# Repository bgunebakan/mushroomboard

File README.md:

# mushroomboard
Mushroom Board is a single board Computer

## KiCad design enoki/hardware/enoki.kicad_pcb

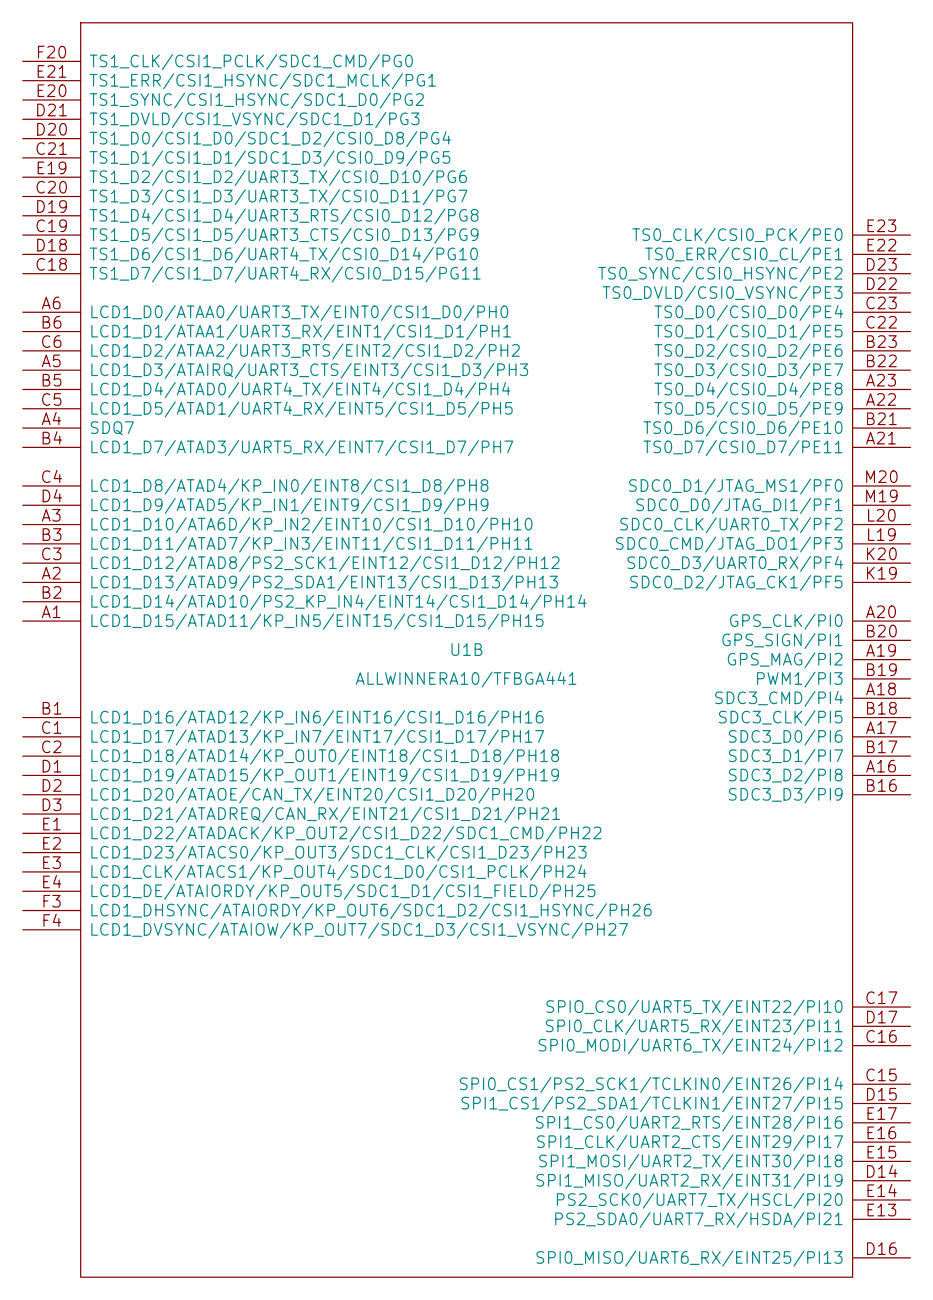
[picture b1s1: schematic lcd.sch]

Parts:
U1: ALLWINNERA10/TFBGA441

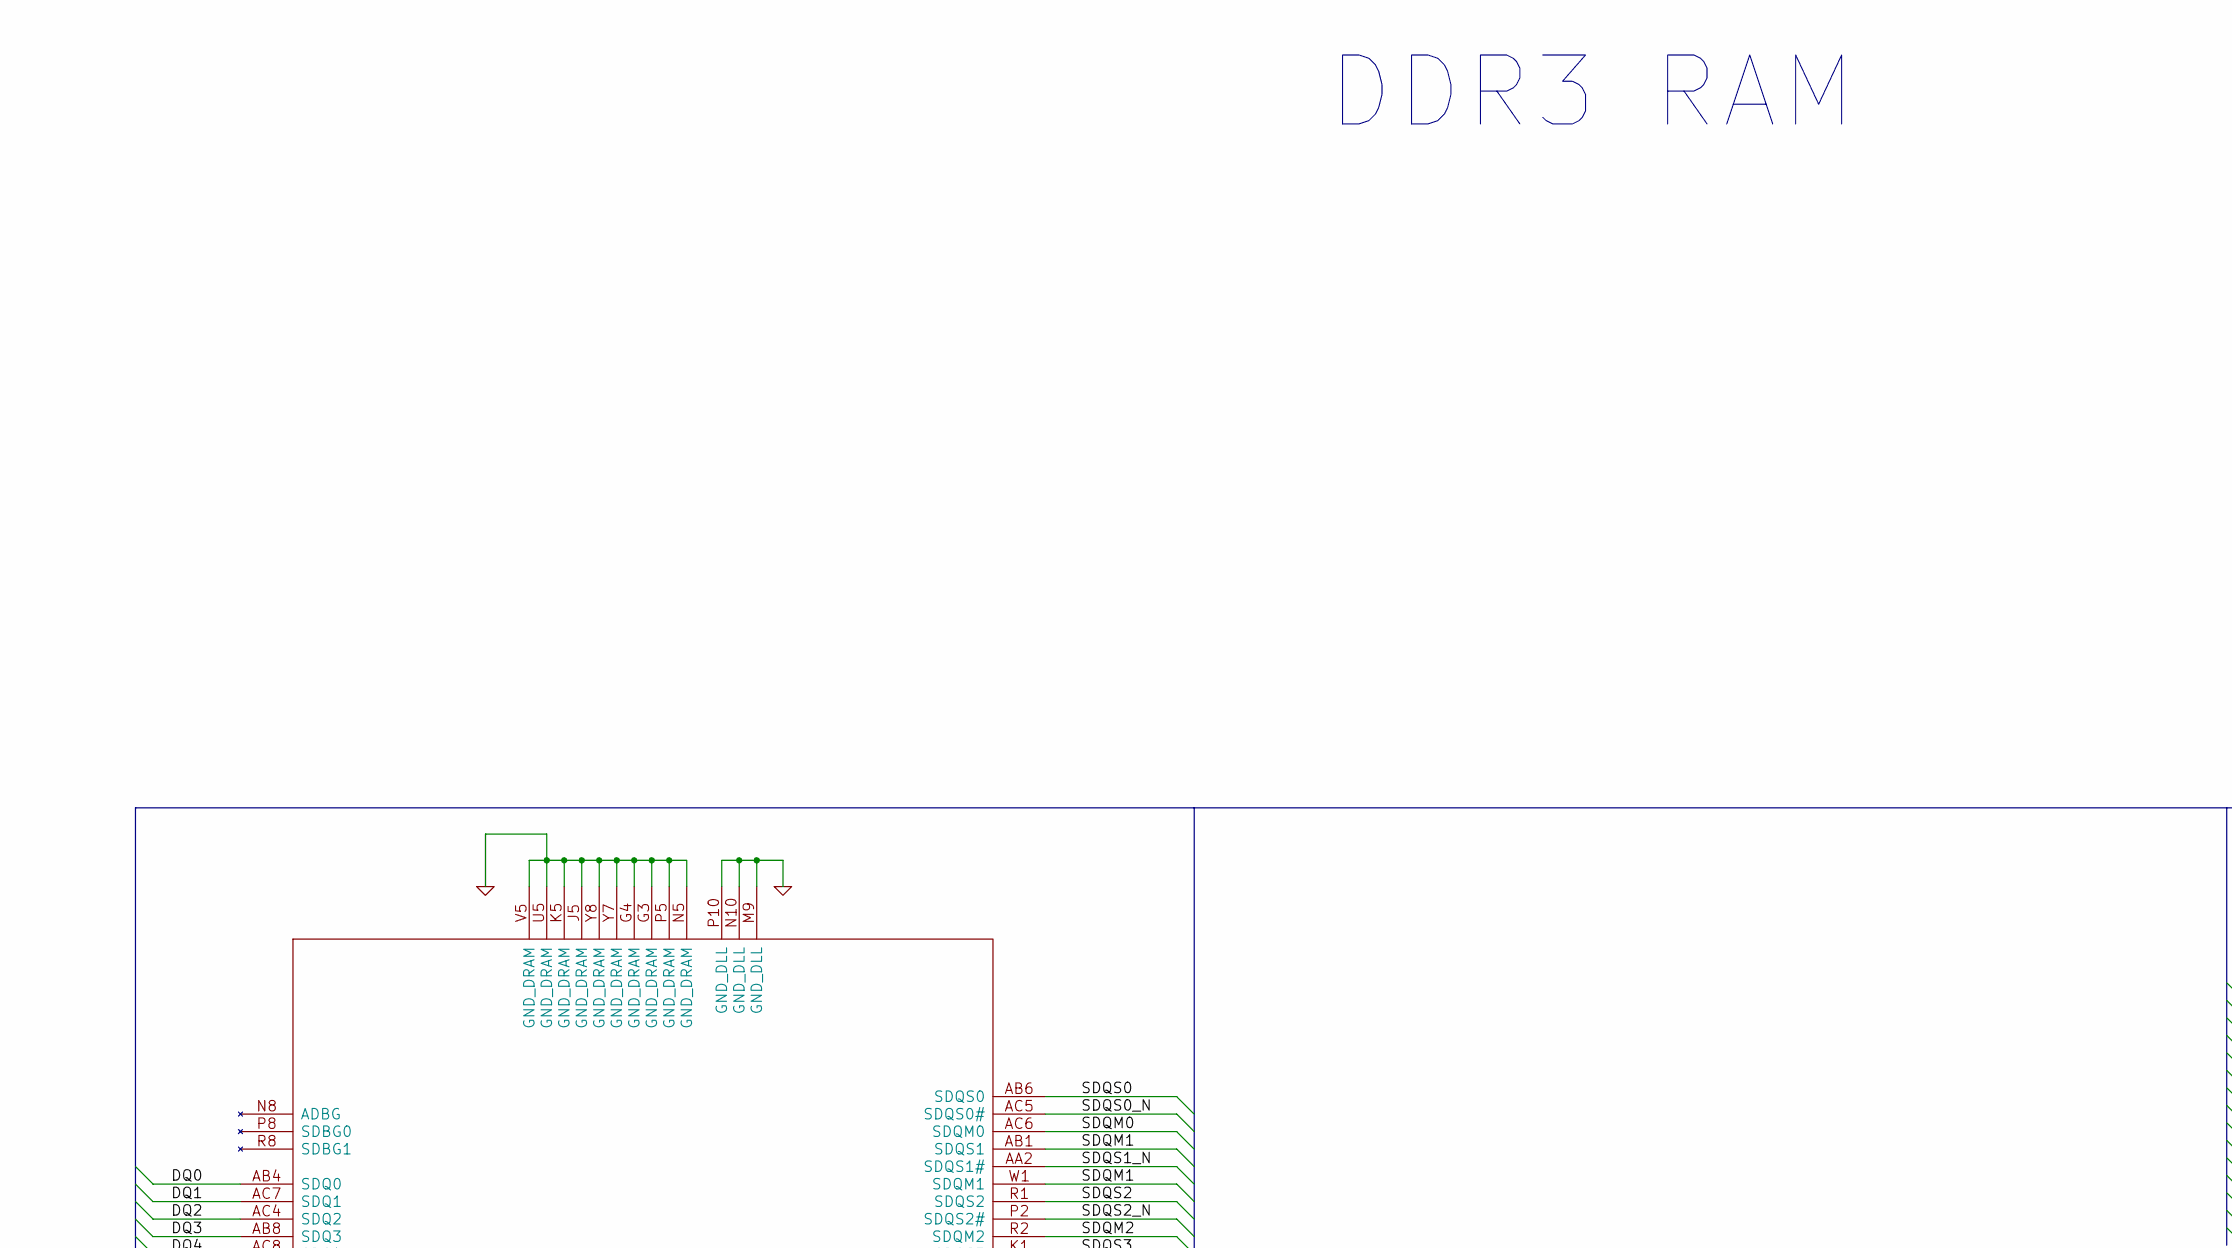
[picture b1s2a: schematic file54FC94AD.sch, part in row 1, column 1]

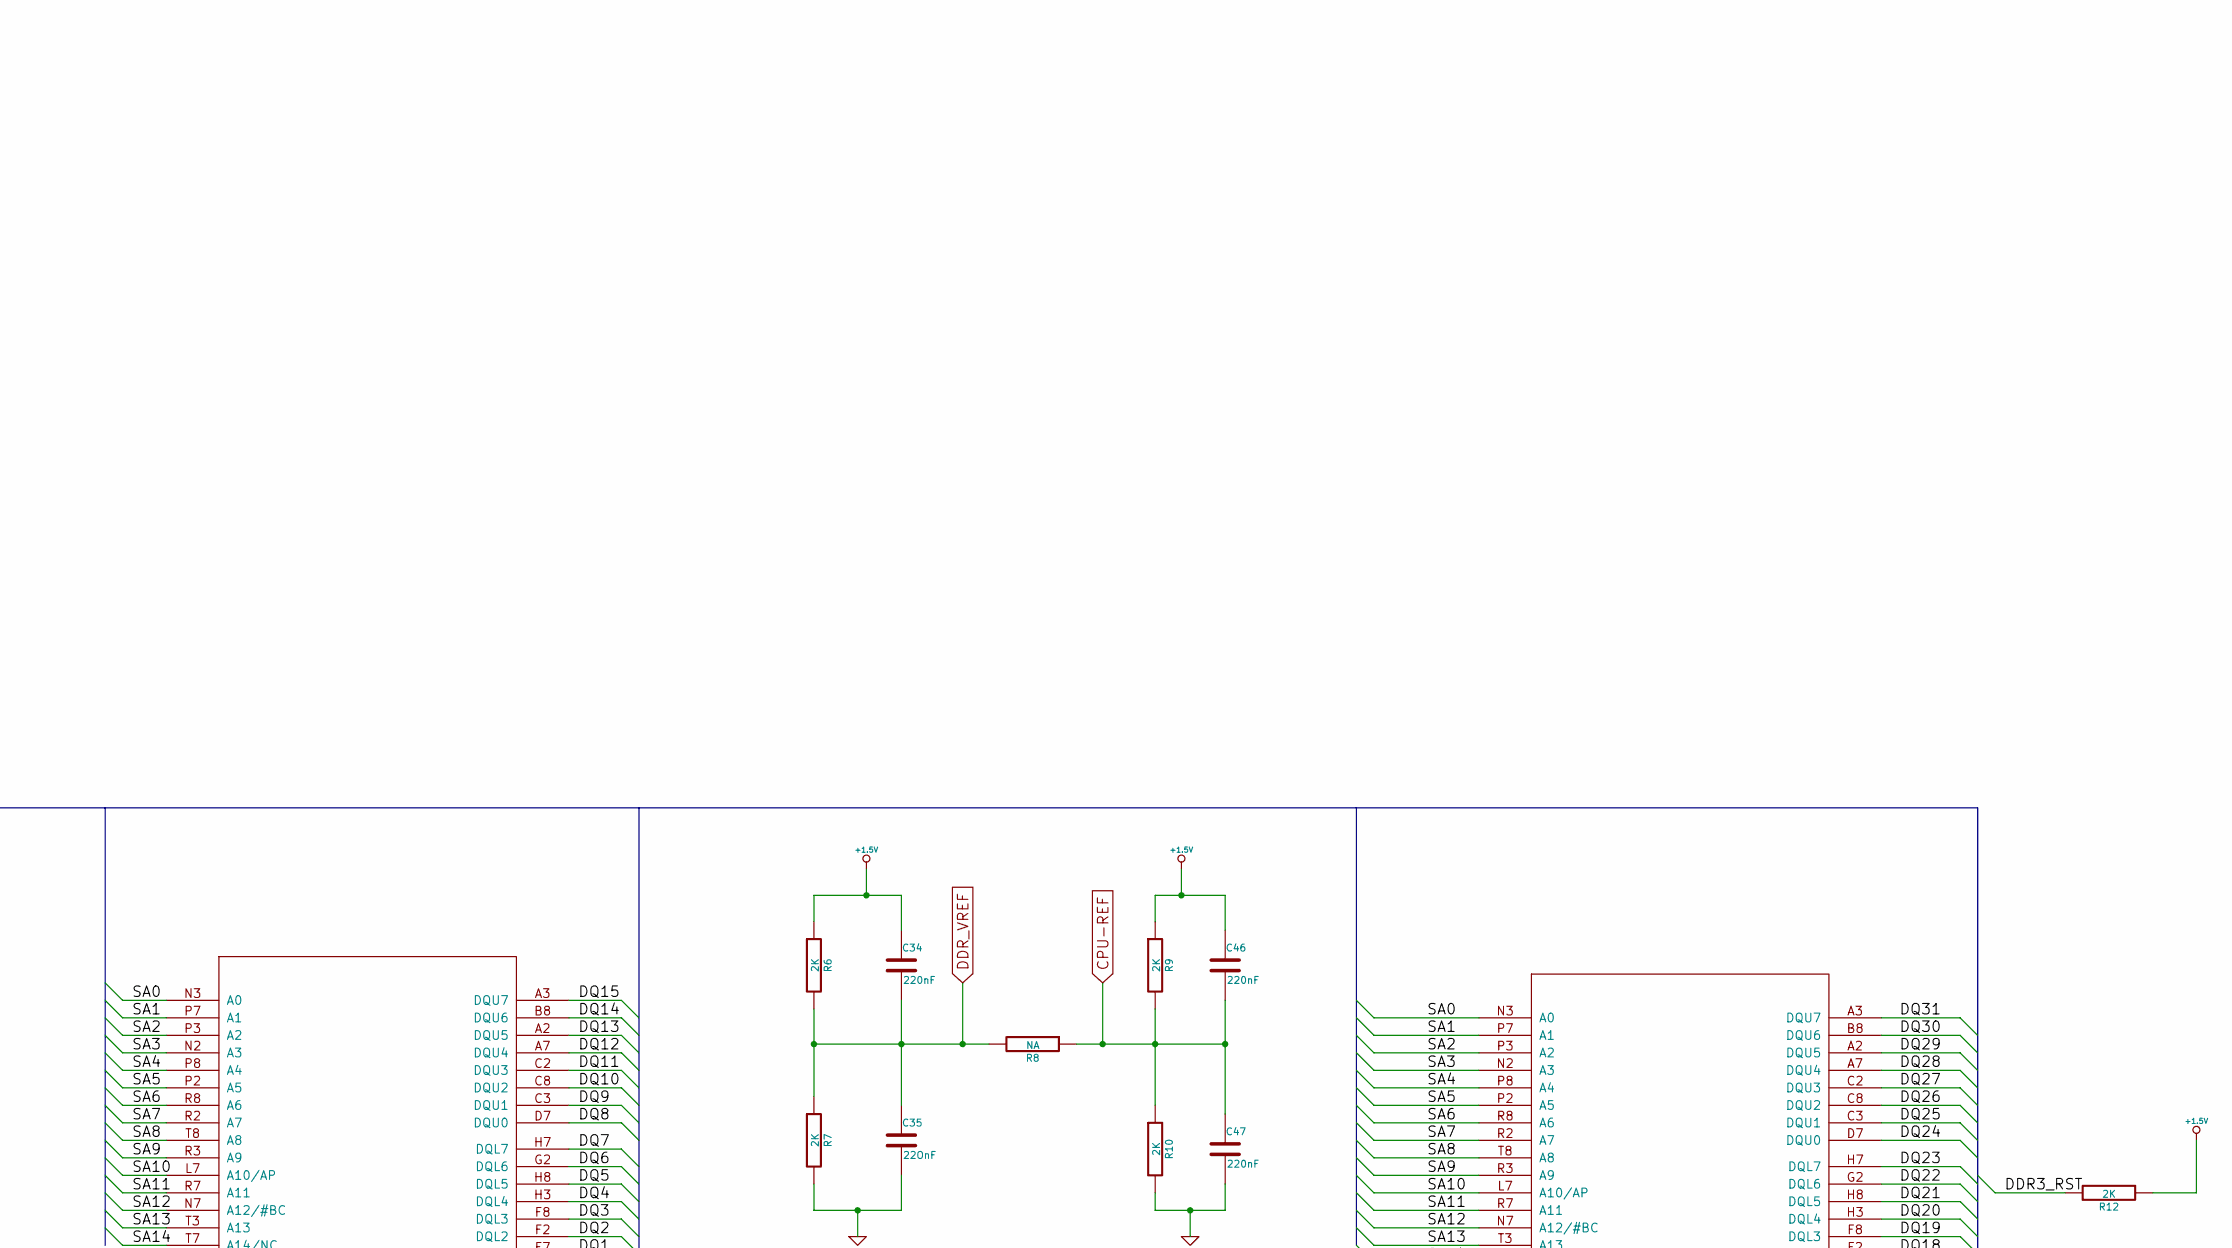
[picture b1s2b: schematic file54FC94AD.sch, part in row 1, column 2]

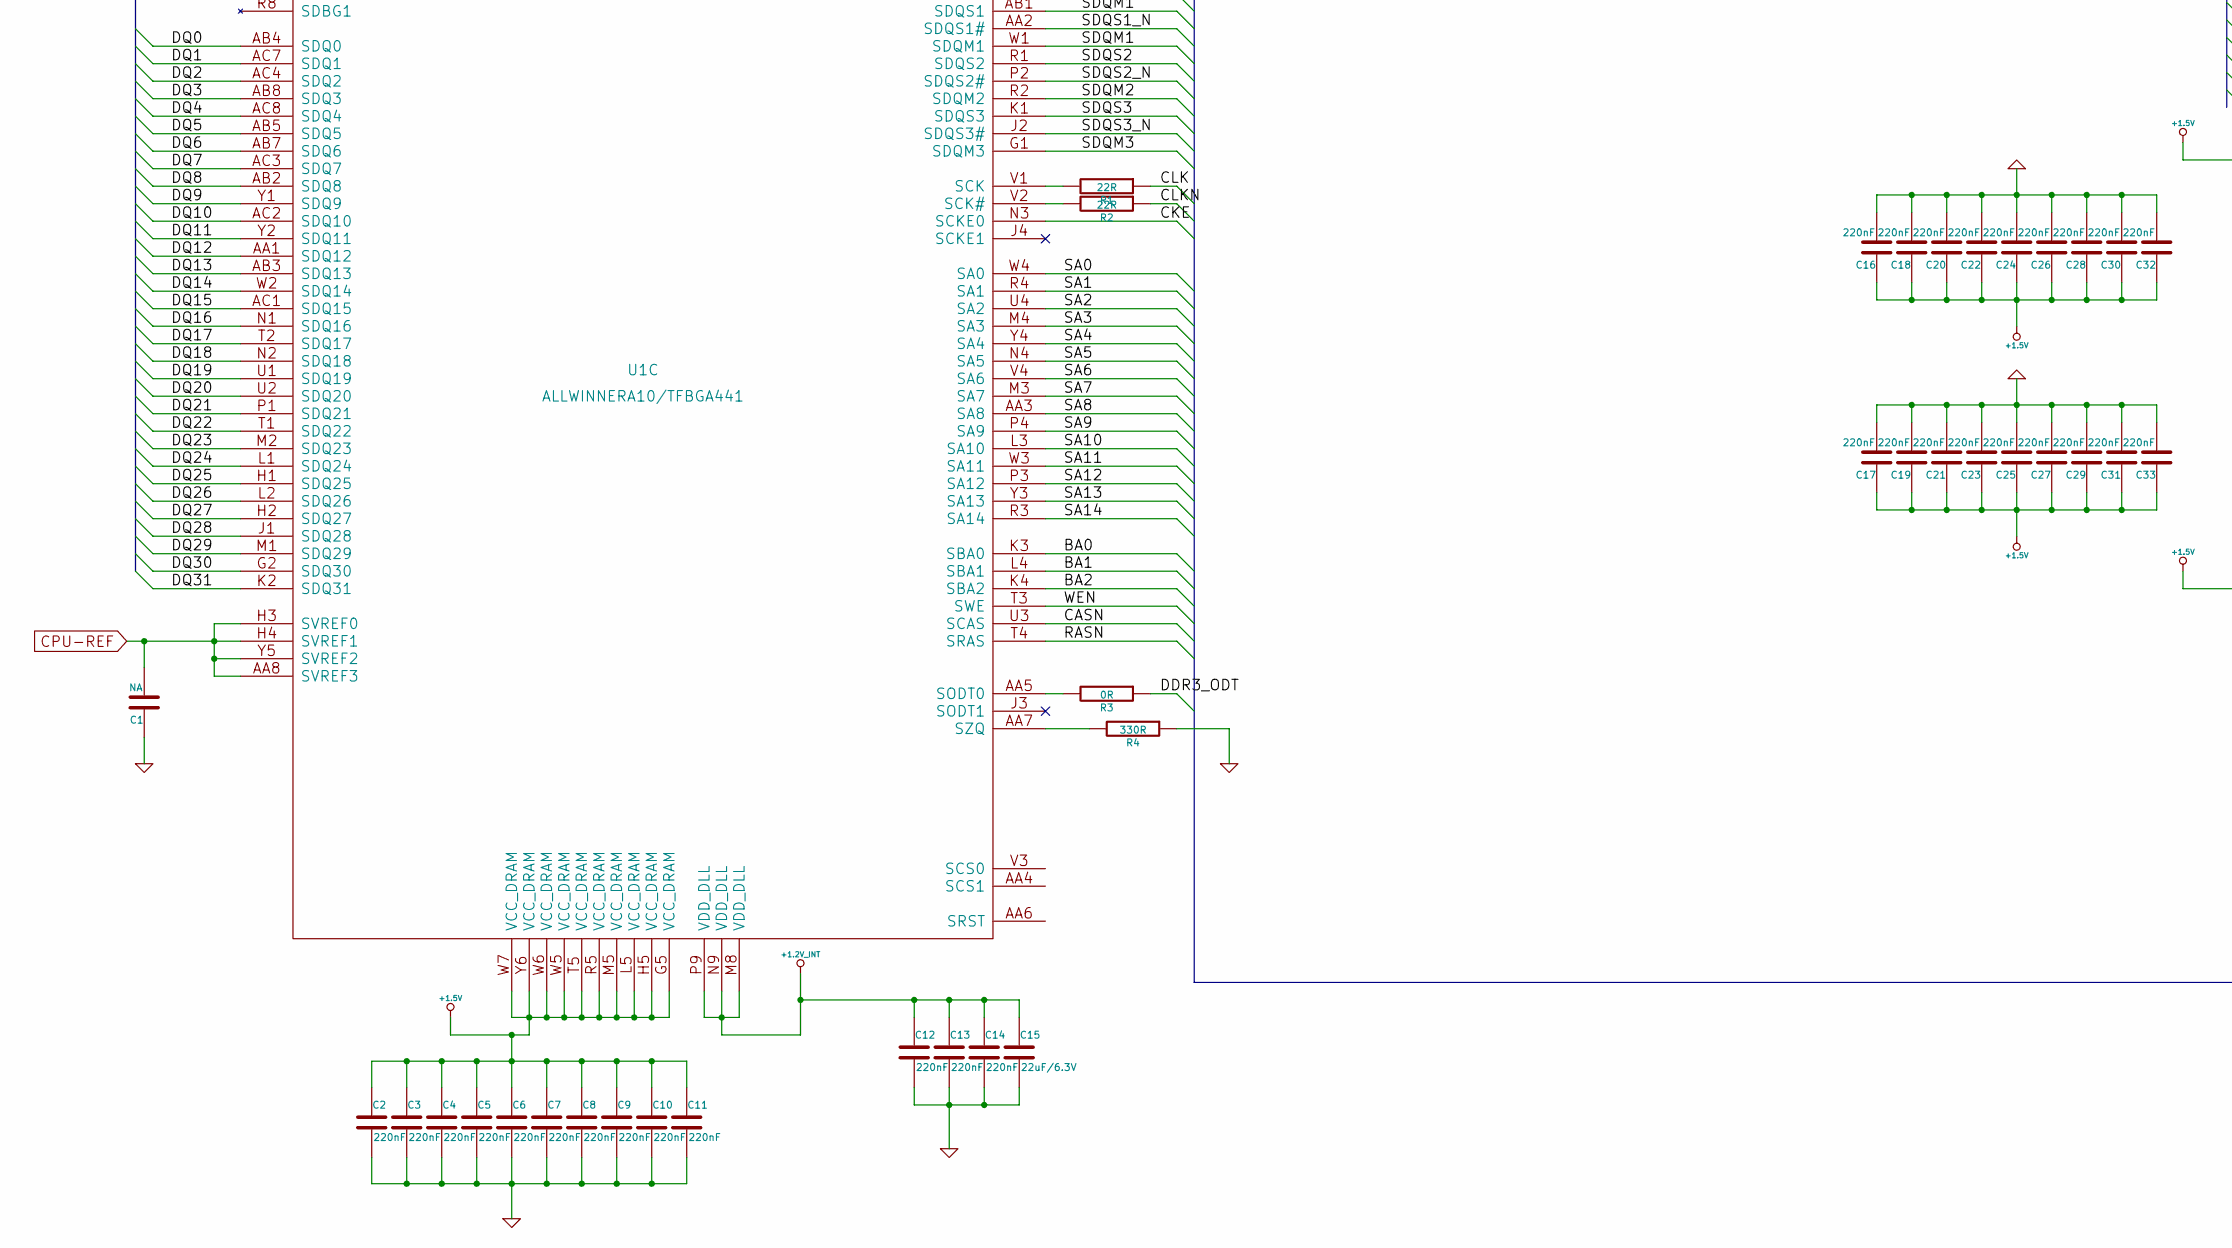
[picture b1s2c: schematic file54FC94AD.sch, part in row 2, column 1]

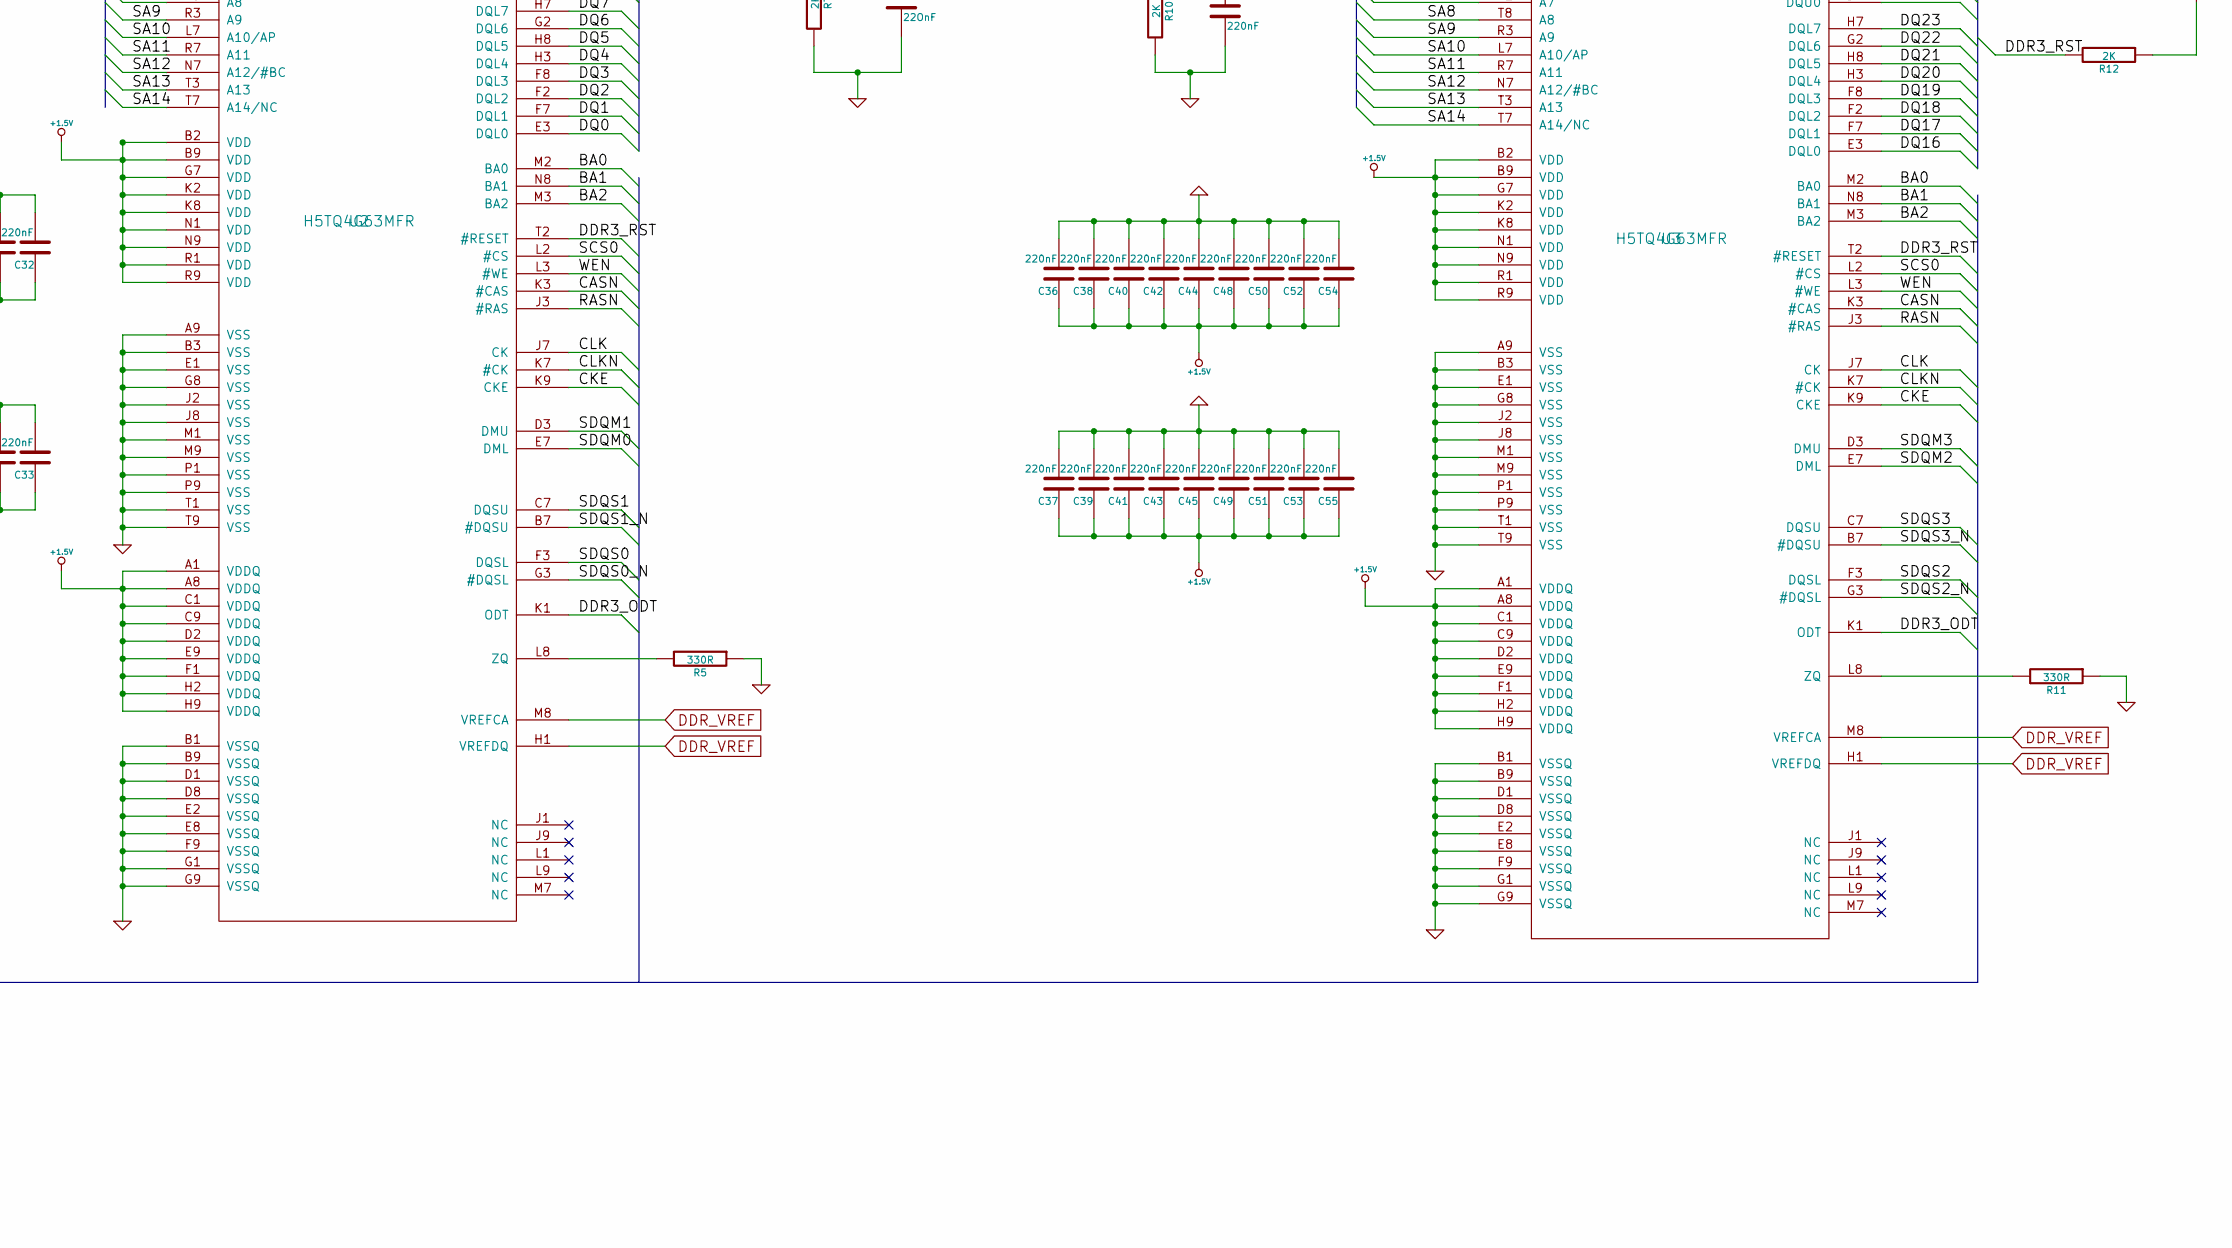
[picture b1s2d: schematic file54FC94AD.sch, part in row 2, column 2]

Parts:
C1: NA
C2, C3, C4, C5, C6, C7, C8, C9, C10, C11, C12, C13, C14, C16, C17, C18, C19, C20, C21, C22, C23, C24, C25, C26, C27, C28, C29, C30, C31, C32, C33, C34, C36, C37, C38, C39, C40, C41, C42, C43, C44, C45, C46, C47, C48, C49, C50, C51, C52, C53, C54, C55: 220nF
C15: 22uF/6.3V
C35: 22OnF
R1, R2: 22R
R3: 0R
R4, R5, R11: 330R
R6, R7, R9, R10, R12: 2K
R8: NA
U1: ALLWINNERA10/TFBGA441
U2, U3: H5TQ4G63MFR

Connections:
+1.2V_INT: C12.1, C13.1, C14.1, C15.1, U1.M8 (VDD_DLL), U1.N9 (VDD_DLL), U1.P9 (VDD_DLL)
/Sheet54FC94AD/BA0: U1.K3 (SBA0), U2.M2 (BA0), U3.M2 (BA0)
/Sheet54FC94AD/BA1: U1.L4 (SBA1), U2.N8 (BA1), U3.N8 (BA1)
/Sheet54FC94AD/BA2: U1.K4 (SBA2), U2.M3 (BA2), U3.M3 (BA2)
/Sheet54FC94AD/CASN: U1.U3 (SCAS), U2.K3 (#CAS), U3.K3 (#CAS)
/Sheet54FC94AD/CKE: U1.N3 (SCKE0), U2.K9 (CKE), U3.K9 (CKE)
/Sheet54FC94AD/CLK: R1.1, U2.J7 (CK), U3.J7 (CK)
/Sheet54FC94AD/CLKN: R2.1, U2.K7 (#CK), U3.K7 (#CK)
/Sheet54FC94AD/DDR3_ODT: R3.1, U2.K1 (ODT), U3.K1 (ODT)
/Sheet54FC94AD/DDR3_RST: R12.2, U2.T2 (#RESET), U3.T2 (#RESET)
/Sheet54FC94AD/DQ0: U1.AB4 (SDQ0), U2.E3 (DQL0)
/Sheet54FC94AD/DQ1: U1.AC7 (SDQ1), U2.F7 (DQL1)
/Sheet54FC94AD/DQ2: U1.AC4 (SDQ2), U2.F2 (DQL2)
/Sheet54FC94AD/DQ3: U1.AB8 (SDQ3), U2.F8 (DQL3)
/Sheet54FC94AD/DQ4: U1.AC8 (SDQ4), U2.H3 (DQL4)
/Sheet54FC94AD/DQ5: U1.AB5 (SDQ5), U2.H8 (DQL5)
/Sheet54FC94AD/DQ6: U1.AB7 (SDQ6), U2.G2 (DQL6)
/Sheet54FC94AD/DQ7: U1.AC3 (SDQ7), U2.H7 (DQL7)
/Sheet54FC94AD/DQ8: U1.AB2 (SDQ8), U2.D7 (DQU0)
/Sheet54FC94AD/DQ9: U1.Y1 (SDQ9), U2.C3 (DQU1)
/Sheet54FC94AD/DQ10: U1.AC2 (SDQ10), U2.C8 (DQU2)
/Sheet54FC94AD/DQ11: U1.Y2 (SDQ11), U2.C2 (DQU3)
/Sheet54FC94AD/DQ12: U1.AA1 (SDQ12), U2.A7 (DQU4)
/Sheet54FC94AD/DQ13: U1.AB3 (SDQ13), U2.A2 (DQU5)
/Sheet54FC94AD/DQ14: U1.W2 (SDQ14), U2.B8 (DQU6)
/Sheet54FC94AD/DQ15: U1.AC1 (SDQ15), U2.A3 (DQU7)
/Sheet54FC94AD/DQ16: U1.N1 (SDQ16), U3.E3 (DQL0)
/Sheet54FC94AD/DQ17: U1.T2 (SDQ17), U3.F7 (DQL1)
/Sheet54FC94AD/DQ18: U1.N2 (SDQ18), U3.F2 (DQL2)
/Sheet54FC94AD/DQ19: U1.U1 (SDQ19), U3.F8 (DQL3)
/Sheet54FC94AD/DQ20: U1.U2 (SDQ20), U3.H3 (DQL4)
/Sheet54FC94AD/DQ21: U1.P1 (SDQ21), U3.H8 (DQL5)
/Sheet54FC94AD/DQ22: U1.T1 (SDQ22), U3.G2 (DQL6)
/Sheet54FC94AD/DQ23: U1.M2 (SDQ23), U3.H7 (DQL7)
/Sheet54FC94AD/DQ24: U1.L1 (SDQ24), U3.D7 (DQU0)
/Sheet54FC94AD/DQ25: U1.H1 (SDQ25), U3.C3 (DQU1)
/Sheet54FC94AD/DQ26: U1.L2 (SDQ26), U3.C8 (DQU2)
/Sheet54FC94AD/DQ27: U1.H2 (SDQ27), U3.C2 (DQU3)
/Sheet54FC94AD/DQ28: U1.J1 (SDQ28), U3.A7 (DQU4)
/Sheet54FC94AD/DQ29: U1.M1 (SDQ29), U3.A2 (DQU5)
/Sheet54FC94AD/DQ30: U1.G2 (SDQ30), U3.B8 (DQU6)
/Sheet54FC94AD/DQ31: U1.K2 (SDQ31), U3.A3 (DQU7)
/Sheet54FC94AD/RASN: U1.T4 (SRAS), U2.J3 (#RAS), U3.J3 (#RAS)
/Sheet54FC94AD/SA0: U1.W4 (SA0), U2.N3 (A0), U3.N3 (A0)
/Sheet54FC94AD/SA1: U1.R4 (SA1), U2.P7 (A1), U3.P7 (A1)
/Sheet54FC94AD/SA2: U1.U4 (SA2), U2.P3 (A2), U3.P3 (A2)
/Sheet54FC94AD/SA3: U1.M4 (SA3), U2.N2 (A3), U3.N2 (A3)
/Sheet54FC94AD/SA4: U1.Y4 (SA4), U2.P8 (A4), U3.P8 (A4)
/Sheet54FC94AD/SA5: U1.N4 (SA5), U2.P2 (A5), U3.P2 (A5)
/Sheet54FC94AD/SA6: U1.V4 (SA6), U2.R8 (A6), U3.R8 (A6)
/Sheet54FC94AD/SA7: U1.M3 (SA7), U2.R2 (A7), U3.R2 (A7)
/Sheet54FC94AD/SA8: U1.AA3 (SA8), U2.T8 (A8), U3.T8 (A8)
/Sheet54FC94AD/SA9: U1.P4 (SA9), U2.R3 (A9), U3.R3 (A9)
/Sheet54FC94AD/SA10: U1.L3 (SA10), U2.L7 (A10/AP), U3.L7 (A10/AP)
/Sheet54FC94AD/SA11: U1.W3 (SA11), U2.R7 (A11), U3.R7 (A11)
/Sheet54FC94AD/SA12: U1.P3 (SA12), U2.N7 (A12/#BC), U3.N7 (A12/#BC)
/Sheet54FC94AD/SA13: U1.Y3 (SA13), U2.T3 (A13), U3.T3 (A13)
/Sheet54FC94AD/SA14: U1.R3 (SA14), U2.T7 (A14/NC), U3.T7 (A14/NC)
/Sheet54FC94AD/SCS0: U2.L2 (#CS), U3.L2 (#CS)
/Sheet54FC94AD/SDQM0: U1.AC6 (SDQM0), U2.E7 (DML)
/Sheet54FC94AD/SDQM1: U1.AB1 (SDQS1), U1.W1 (SDQM1), U2.D3 (DMU)
/Sheet54FC94AD/SDQM2: U1.R2 (SDQM2), U3.E7 (DML)
/Sheet54FC94AD/SDQM3: U1.G1 (SDQM3), U3.D3 (DMU)
/Sheet54FC94AD/SDQS0: U1.AB6 (SDQS0), U2.F3 (DQSL)
/Sheet54FC94AD/SDQS0_N: U1.AC5 (SDQS0#), U2.G3 (#DQSL)
/Sheet54FC94AD/SDQS1: U2.C7 (DQSU)
/Sheet54FC94AD/SDQS1_N: U1.AA2 (SDQS1#), U2.B7 (#DQSU)
/Sheet54FC94AD/SDQS2: U1.R1 (SDQS2), U3.F3 (DQSL)
/Sheet54FC94AD/SDQS2_N: U1.P2 (SDQS2#), U3.G3 (#DQSL)
/Sheet54FC94AD/SDQS3: U1.K1 (SDQS3), U3.C7 (DQSU)
/Sheet54FC94AD/SDQS3_N: U1.J2 (SDQS3#), U3.B7 (#DQSU)
/Sheet54FC94AD/WEN: U1.T3 (SWE), U2.L3 (#WE), U3.L3 (#WE)
CPU-REF: C1.2, C46.2, C47.1, R8.1, R9.2, R10.1, U1.AA8 (SVREF3), U1.H3 (SVREF0), U1.H4 (SVREF1), U1.Y5 (SVREF2)
DDR_VREF: C34.2, C35.1, R6.2, R7.1, R8.2, U2.H1 (VREFDQ), U2.M8 (VREFCA), U3.H1 (VREFDQ), U3.M8 (VREFCA)
unnamed: R1.2, U1.V1 (SCK)
unnamed: R2.2, U1.V2 (SCK#)
unnamed: R3.2, U1.AA5 (SODT0)
unnamed: R4.2, U1.AA7 (SZQ)
unnamed: R5.2, U2.L8 (ZQ)
unnamed: R11.2, U3.L8 (ZQ)

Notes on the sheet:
DDR3 RAM

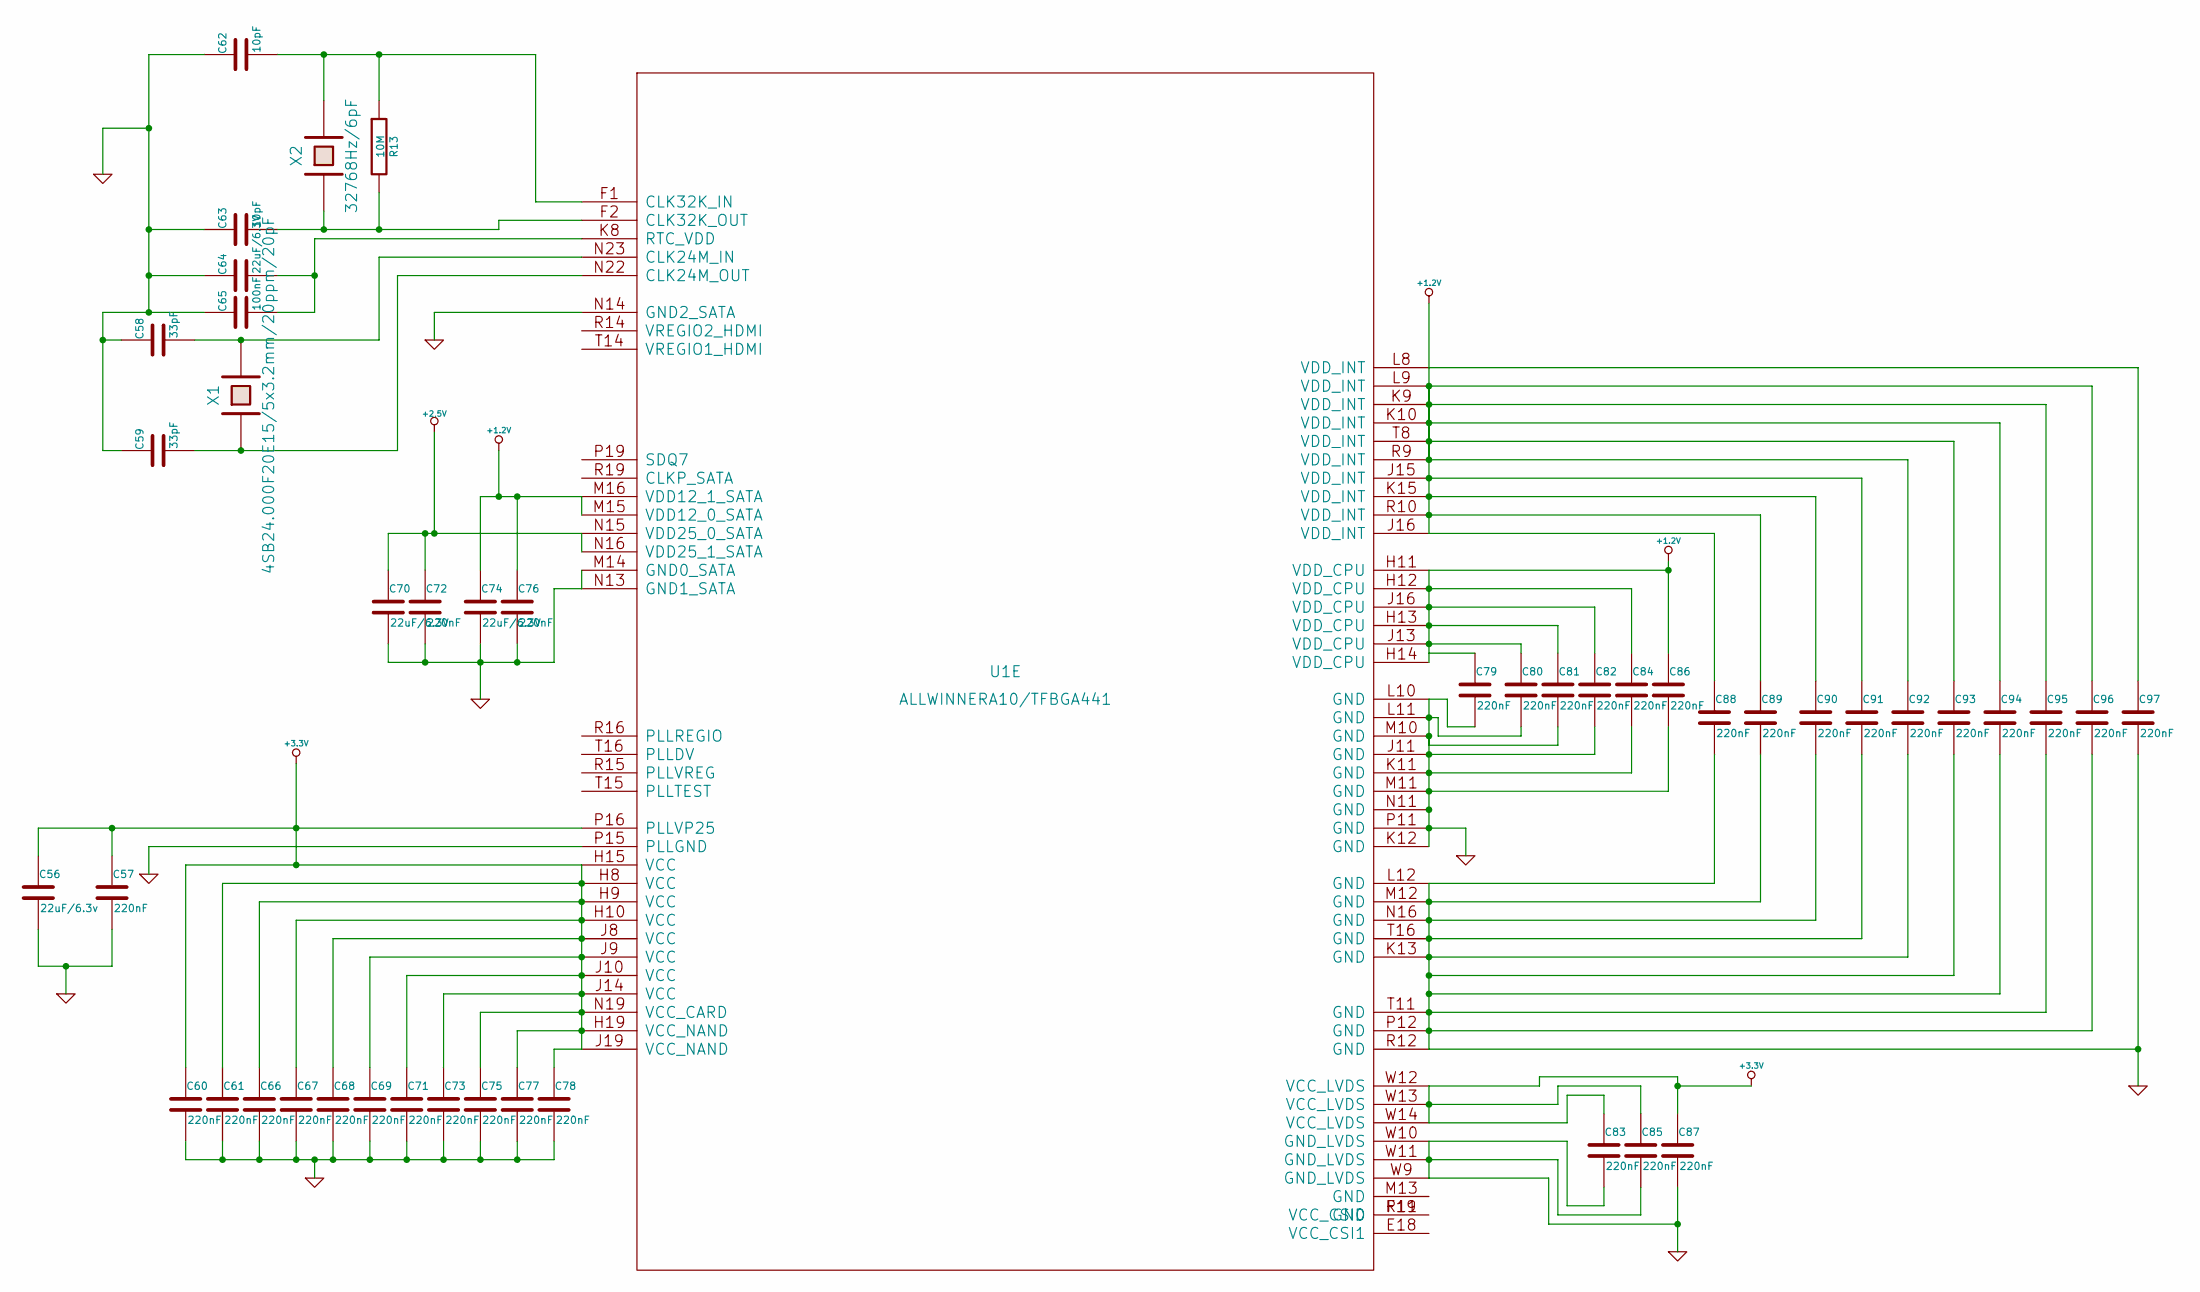
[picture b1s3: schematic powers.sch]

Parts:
C56: 22uF/6.3v
C57, C60, C61, C66, C67, C68, C69, C71, C72, C73, C75, C76, C77, C78, C79, C80, C81, C82, C83, C84, C85, C86, C87, C88, C89, C90, C91, C92, C93, C94, C95, C96, C97: 220nF
C58, C59: 33pF
C62, C63: 10pF
C64, C70, C74: 22uF/6.3V
C65: 100nF
R13: 10M
U1: ALLWINNERA10/TFBGA441
X1: 4SB24.000F20E15/5x3.2mm/20ppm/20pF
X2: 32768Hz/6pF

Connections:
+1.2V: C74.1, C76.1, C80.1, C81.1, C82.1, C84.1, C86.1, C88.1, C89.1, C90.1, C91.1, C92.1, C93.1, C94.1, C95.1, C96.1, U1.H11 (VDD_CPU), U1.H12 (VDD_CPU), U1.H13 (VDD_CPU), U1.H14 (VDD_CPU), U1.J13 (VDD_CPU), U1.J15 (VDD_INT), U1.J16 (VDD_CPU), U1.K9 (VDD_INT), U1.K10 (VDD_INT), U1.K15 (VDD_INT), U1.L9 (VDD_INT), U1.M15 (VDD12_0_SATA), U1.M16 (VDD12_1_SATA), U1.R9 (VDD_INT), U1.R10 (VDD_INT), U1.T8 (VDD_INT)
+3.3V: C56.1, C57.1, C60.1, C61.1, C66.1, C67.1, C68.1, C69.1, C71.1, C73.1, C75.1, C77.1, C78.1, C83.1, C85.1, C87.1, U1.H8 (VCC), U1.H9 (VCC), U1.H10 (VCC), U1.H15 (VCC), U1.H19 (VCC_NAND), U1.J8 (VCC), U1.J9 (VCC), U1.J10 (VCC), U1.J14 (VCC), U1.J19 (VCC_NAND), U1.N19 (VCC_CARD), U1.P16 (PLLVP25), U1.W12 (VCC_LVDS), U1.W13 (VCC_LVDS), U1.W14 (VCC_LVDS)
unnamed: C58.2, U1.N23 (CLK24M_IN), X1.2
unnamed: C59.2, U1.N22 (CLK24M_OUT), X1.1
unnamed: C62.2, R13.1, U1.F1 (CLK32K_IN), X2.2
unnamed: C63.2, R13.2, U1.F2 (CLK32K_OUT), X2.1
unnamed: C64.2, C65.2, U1.K8 (RTC_VDD)
unnamed: C97.1, U1.L8 (VDD_INT)
unnamed: U1.F19 (VCC_CSI0), U1.R11 (GND)

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
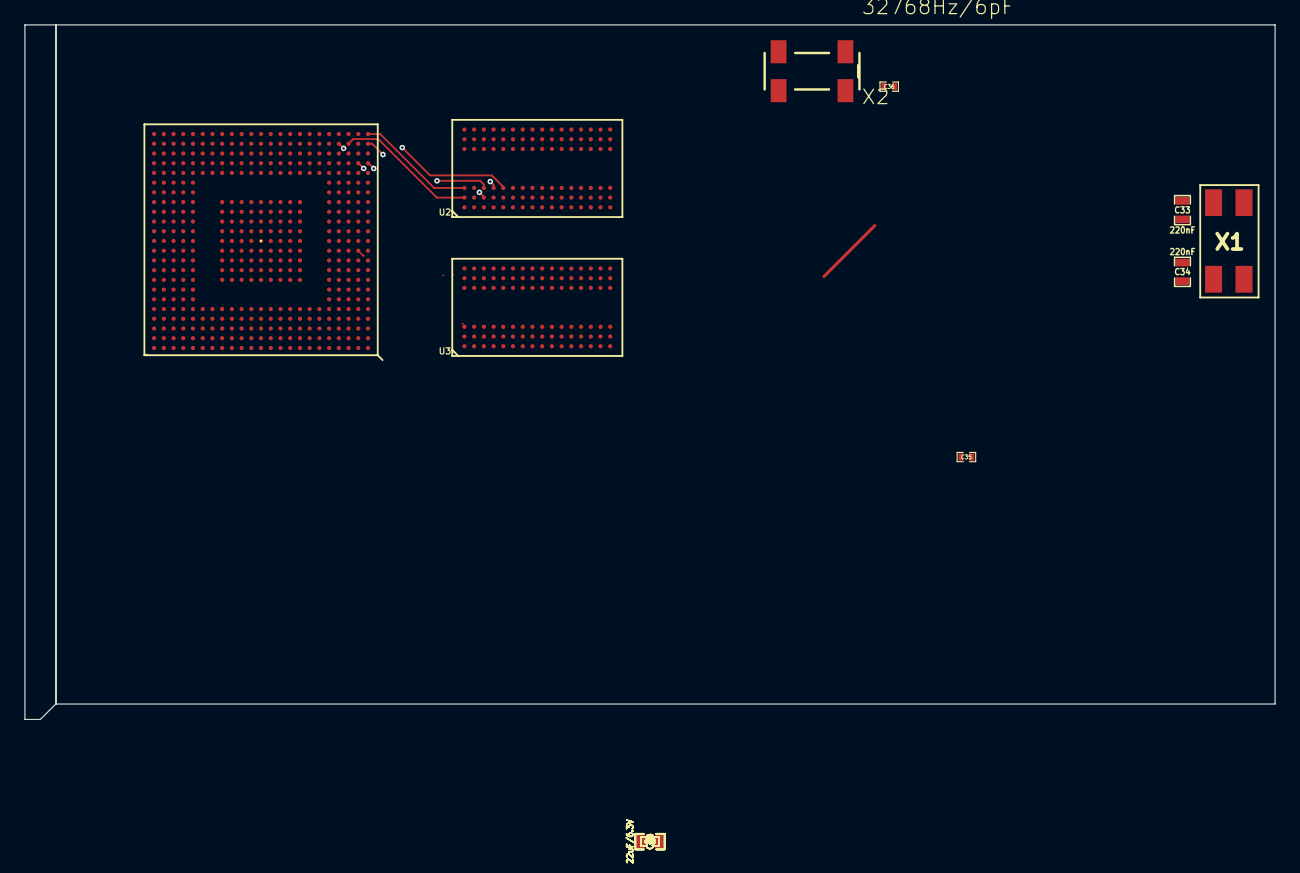
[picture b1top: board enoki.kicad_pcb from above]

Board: 4 copper layers, 102.9 x 57.1 mm, 115 parts (0 on the bottom side), 91 nets.

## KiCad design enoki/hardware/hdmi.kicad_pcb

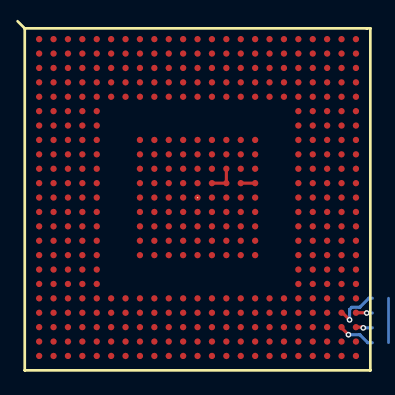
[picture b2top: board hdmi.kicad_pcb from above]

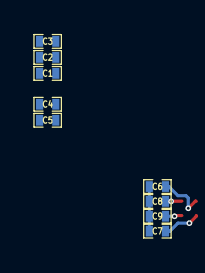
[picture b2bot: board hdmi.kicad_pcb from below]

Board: 4 copper layers, 10 parts (9 on the bottom side), 7 nets.

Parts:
C1, C4: 22uF/6.3V; SM0402_c
C2: C; SM0402_c
C3, C5: 220nF; SM0402_c
C6, C7, C8, C9: 1nF; SM0402_c
U1: ALLWINNERA10/TFBGA441; TFBGA441-new

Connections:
+1.2V: C4.1, C5.1, U1.K16
+3.3V: C1.1, C2.1, C3.1, U1.L15, U1.L16
GND: C1.2, C2.2, C3.2, C4.2, C5.2, C6.2, C7.2, C8.2, C9.2, U1.K14, U1.L13, U1.L14
unnamed: C6.1, U1.Y22
unnamed: C8.1, U1.Y23
unnamed: C7.1, U1.AA22
unnamed: C9.1, U1.AA23
